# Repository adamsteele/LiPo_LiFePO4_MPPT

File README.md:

LiPo LiFePO4 MPPT
=================

This is a basic MPPT charger currently setup to do 3S LiPo batteries based on the LT3652 chip.

This is mostly a copy of this http://www.mictronics.de/projects/solar-cell-mppt/ project. It just didn't have nice eagle schematics or a completed BOM.

I've built and tested this board and it mostly works. What didn't work for me are the status LEDs, I haven't figured out why.

The board should be stackable to provide a higher current rating, but I haven't tested it. Linear Electronics has some app notes on the subject that I recommend reading. The stackable boards don't need to be fully populated.

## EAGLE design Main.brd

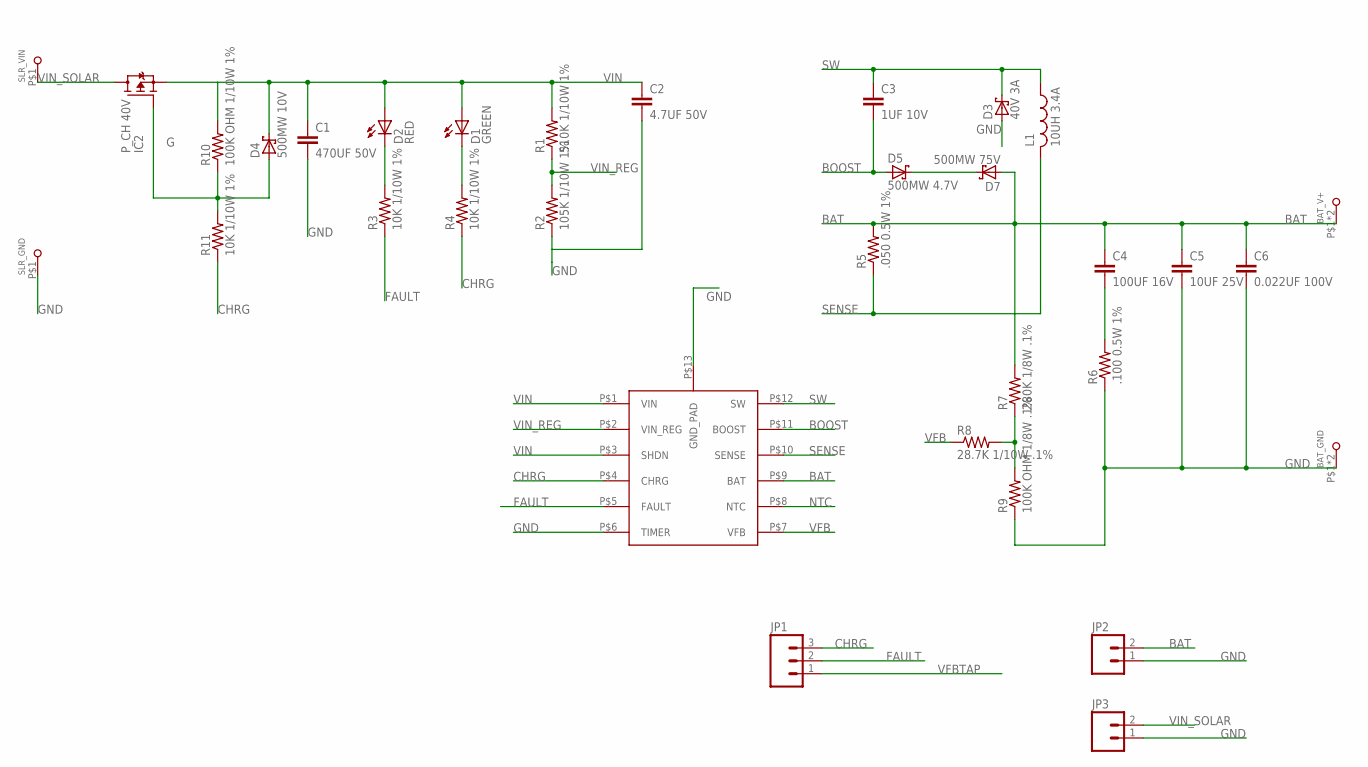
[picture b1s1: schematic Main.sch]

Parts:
BAT_GND: LARGE_PADMED_PAD_PAIR; MEDIUM_PAD_PAIR
BAT_V+: LARGE_PADMED_PAD_PAIR; MEDIUM_PAD_PAIR
C1: 470UF 50V; 5X5_CAP_HOLES
C2: 4.7UF 50V; C1210
C3: 1UF 10V; C0805
C4: 100UF 16V; C1210
C5: 10UF 25V; C1210
C6: 0.022UF 100V; C0805
D1: GREEN; SML0603
D2: RED; SML0603
D3: 40V 3A; SMC
D4: 500MW 10V; MINIMELF
D5: 500MW 4.7V; MINIMELF
D7: 500MW 75V; MINIMELF
IC1: LT3652MSE-12-MIGHT-BE-HAND-DOOABLE; MSE_12_HANDSOLDERABLE
IC2: P_CH 40V; SO-8_SOIC8
JP1: M03LOCK; 1X03_LOCK
JP2, JP3: M02LOCK; 1X02_LOCK
L1: 10UH 3.4A; ECOS_INDUCTOR_SMT
R1: 510K 1/10W 1%; R0603
R2: 105K 1/10W 1%; R0603
R3, R4, R11: 10K 1/10W 1%; R0603
R5: .050 0.5W 1%; R1206
R6: .100 0.5W 1%; R1206
R7: 280K 1/8W .1%; R0805
R8: 28.7K 1/10W .1%; R0603
R9: 100K OHM 1/8W .1%; R0805
R10: 100K OHM 1/10W 1%; R0603
SLR_GND: LARGE_PADMED_PAD; MEDIUM_PAD
SLR_VIN: LARGE_PADMED_PAD; MEDIUM_PAD

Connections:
BAT: BAT_V+.P$1, BAT_V+.P$2, C4.1, C5.1, C6.1, D7.P$1 (A), IC1.P$9 (BAT), JP2.2, R5.2, R7.2
BOOST: C3.2, D5.P$1 (A), IC1.P$11 (BOOST)
CHRG: IC1.P$4 (CHRG), JP1.3, R4.1, R11.1
FAULT: IC1.P$5 (FAULT), JP1.2, R3.1
G: D4.P$1 (A), IC2.4 (G), R10.1, R11.2
GND: BAT_GND.P$1, BAT_GND.P$2, C1.P$2 (2), C2.2, C5.2, C6.2, D3.A, IC1.P$6 (TIMER), IC1.P$13 (GND_PAD), JP2.1, JP3.1, R2.1, R6.1, R9.1, SLR_GND.P$1
unnamed: D5.P$2 (C), D7.P$2 (C)
unnamed: D2.C, R3.2
unnamed: D1.C, R4.2
unnamed: C4.2, R6.2
NTC: IC1.P$8 (NTC)
SENSE: IC1.P$10 (SENSE), L1.P$2 (2), R5.1
SW: C3.1, D3.C, IC1.P$12 (SW), L1.P$1 (1)
VFB: IC1.P$7 (VFB), R8.1
VFBTAP: JP1.1, R7.1, R8.2, R9.2
VIN: C1.P$1 (1), C2.1, D1.A, D2.A, D4.P$2 (C), IC1.P$1 (VIN), IC1.P$3 (SHDN), IC2.1 (S), IC2.2 (S), IC2.3 (S), R1.2, R10.2
VIN_REG: IC1.P$2 (VIN_REG), R1.1, R2.2
VIN_SOLAR: IC2.5 (D), IC2.6 (D), IC2.7 (D), IC2.8 (D), JP3.2, SLR_VIN.P$1

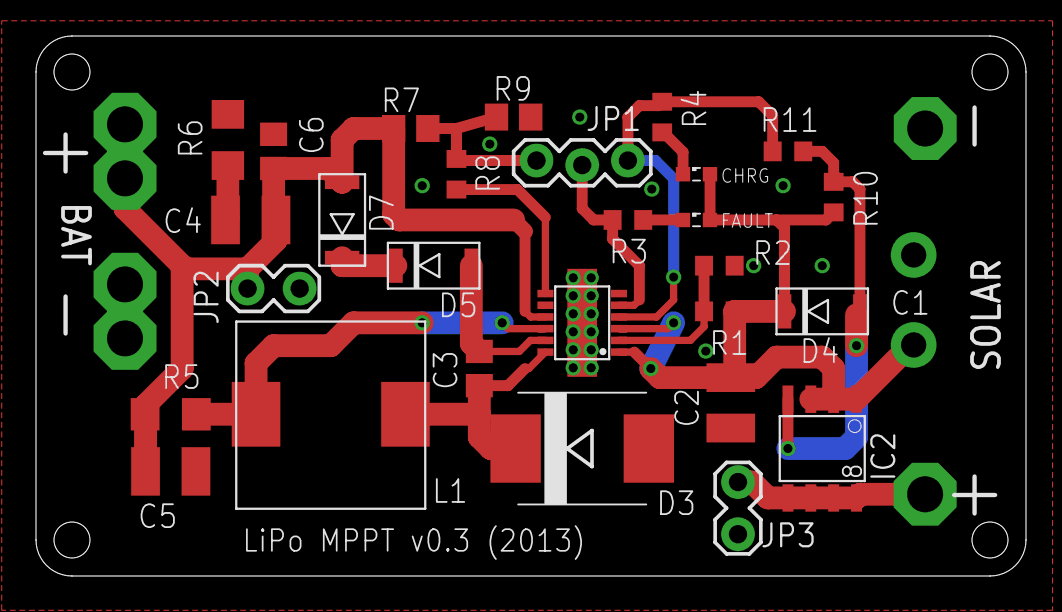
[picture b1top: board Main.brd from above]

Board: 2 copper layers, 55.0 x 30.0 mm, 33 parts (0 on the bottom side), 17 nets.

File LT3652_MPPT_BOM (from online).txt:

Digi-Key Part Number		Quantity	Description							Schematic Numbers
338-1703-ND					1			CAP ALUM 470UF 50V 20% RADIAL		C1
490-1864-1-ND				1			CAP CER 4.7UF 50V 10% X7R 1210		C2
490-1695-1-ND				1			CAP CER 1UF 10V 10% X7R 0805		C3 (don't think we need 10)
587-3152-1-ND				1			CAP CER 100UF 16V 20% X5R 1210		C4
445-1434-1-ND				1			CAP CER 10UF 25V 20% X7R 1210		C5 (replaced with 587-2599-1-ND)
445-1345-1-ND				1			CAP CER 0.022UF 100V X7R 0805		C6
475-2709-1-ND				1			LED SMARTLED GREEN 570NM 0603		D1
475-2506-1-ND				1			LED SMARTLED 630NM RED 0603 SMD		D2
MBRS340T3GOSCT-ND			1			DIODE SCHOTTKY 40V 3A SMC			D3
BZV55C10-TPMSCT-ND			1			DIODE ZENER 500MW 10V MINIMELF		D4
BZV55C4V7-TPMSCT-ND			1			DIODE ZENER 500MW 4.7V MINIMELF		D5
LL4148DICT-ND				1			DIODE SWITCH 75V 500MW MINIMELF		D7 (there is no D6)
LT3652HVEMSE#PBF-ND			1			IC BATTERY CHARGER 2A 12-MSOP		IC1 (replaced with LT3652EMSE#PBF-ND ; it's cheaper)
SI4401DDY-T1-GE3CT-ND		1			MOSFET P-CH 40V 8-SOIC				IC2
495-1796-1-ND				1			INDUCTOR POWER 10UH 3.4A SMD		L1
P510KHCT-ND					1			RES 510K OHM 1/10W 1% 0603 SMD		R1
P105KHCT-ND					1			RES 105K OHM 1/10W 1% 0603 SMD		R2
P10.0KHCT-ND				3			RES 10.0K OHM 1/10W 1% 0603 SMD		R3 R4 R11
989-1029-1-ND				1			RES .050 OHM 0.5W 1% 1206 SMD		R5
989-1031-1-ND				1			RES .100 OHM 0.5W 1% 1206 SMD		R6
RG20P280KBCT-ND				1			RES 280K OHM 1/8W .1% 0805 SMD		R7
P28.7KDBCT-ND				1			RES 28.7K OHM 1/10W .1% 0603 SMD	R8
CRT0805-BY-1003ELFCT-ND		1			RES 100K OHM 1/8W .1% 0805 SMD		R9
P100KHCT-ND					1			RES 100K OHM 1/10W 1% 0603 SMD		R10
P107KHCT-ND					1			RES 107K OHM 1/10W 1% 0603 SMD		not used

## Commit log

2014-03-15 Initial Upload of Files

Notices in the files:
parts and their libraries:
SparkFun-Connectors: Licensing: CC v3.0 Share-Alike You are welcome to use this library for commercial purposes.
